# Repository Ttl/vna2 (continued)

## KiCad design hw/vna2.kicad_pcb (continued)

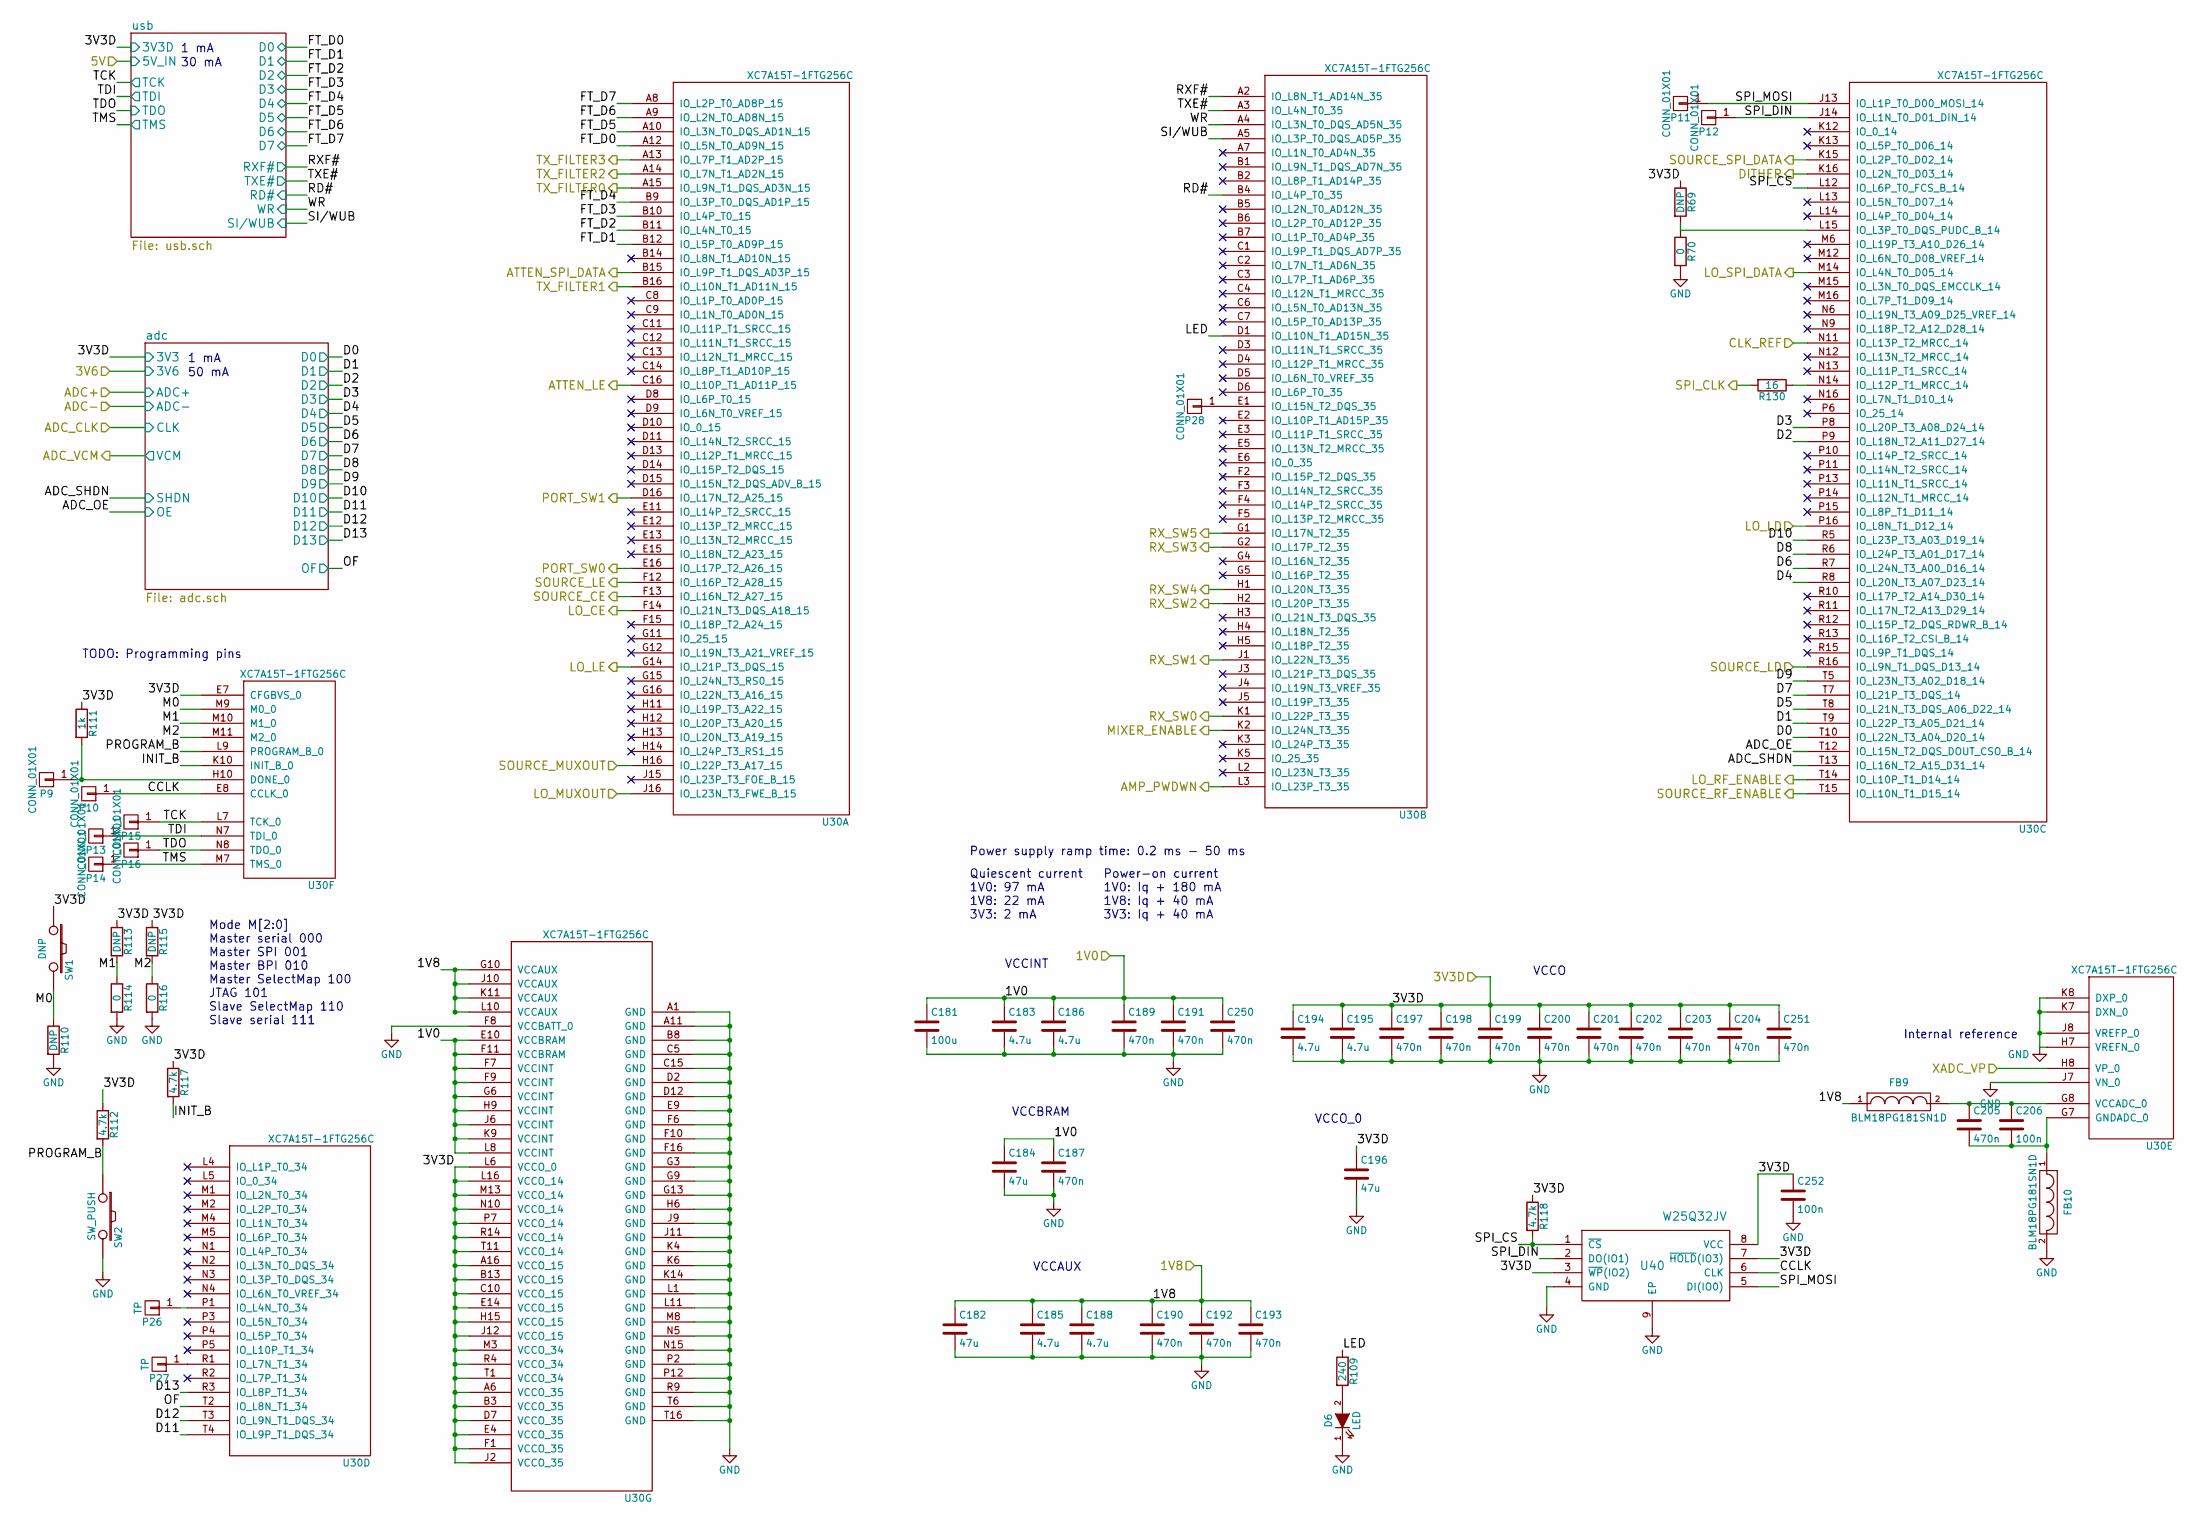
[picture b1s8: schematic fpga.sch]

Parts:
C181: 100u; C_1210
C182, C184, C196: 47u; C_1206
C183, C185, C186, C188, C194, C195: 4.7u; C_0805b
C187, C189, C190, C191, C192, C193, C197, C198, C199, C200, C201, C202, C203, C204, C205, C250, C251: 470n; C_0402b
C206, C252: 100n; C_0402b
D6: LED; LED_0603
FB9, FB10: BLM18PG181SN1D; C_0603b
P9, P10, P11, P12, P13, P14, P15, P16, P28: CONN_01X01; TP_1.00
P26, P27: TP; TP_1.00
R69, R110, R113, R115: DNP; R_0402b
R70, R114, R116: 0; R_0402b
R109: 240; R_0402b
R111: 1k; R_0402b
R112, R117, R118: 4.7k; R_0402b
R130: 16; R_0402b
SW1: DNP; EVP-AWBA2A
SW2: SW_PUSH; EVP-AWBA2A
U30: XC7A15T-1FTG256C; FTG256
U40: W25Q32JV; DFN-S-8-1EP_6x5mm_Pitch1.27mm

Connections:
/1V0: C181.1, C183.1, C184.1, C186.1, C187.1, C189.1, C191.1, C250.1, U30.E10 (VCCBRAM), U30.F7 (VCCINT), U30.F9 (VCCINT), U30.F11 (VCCBRAM), U30.G6 (VCCINT), U30.H9 (VCCINT), U30.J6 (VCCINT), U30.K9 (VCCINT), U30.L8 (VCCINT); also elsewhere on the board
/1V8: C182.1, C185.1, C188.1, C190.1, C192.1, C193.1, FB9.1, U30.G10 (VCCAUX), U30.J10 (VCCAUX), U30.K11 (VCCAUX), U30.L10 (VCCAUX); also elsewhere on the board
/3V3D: C194.1, C195.1, C196.1, C197.1, C198.1, C199.1, C200.1, C201.1, C202.1, C203.1, C204.1, C251.1, C252.1, R69.1, R111.1, R112.1, R113.1, R115.1, R117.1, R118.1, SW1.1, U30.A6 (VCCO_35), U30.A16 (VCCO_15), U30.B3 (VCCO_35), U30.B13 (VCCO_15), U30.C10 (VCCO_15), U30.D7 (VCCO_35), U30.E4 (VCCO_35), U30.E7 (CFGBVS_0), U30.E14 (VCCO_15), U30.F1 (VCCO_35), U30.H15 (VCCO_15), U30.J2 (VCCO_35), U30.J12 (VCCO_15), U30.L6 (VCCO_0), U30.L16 (VCCO_14), U30.M3 (VCCO_34), U30.M13 (VCCO_14), U30.N10 (VCCO_14), U30.P7 (VCCO_14), U30.R4 (VCCO_34), U30.R14 (VCCO_14), U30.T1 (VCCO_34), U30.T11 (VCCO_14), U40.3 (~WP~(IO2)), U40.7 (~HOLD~(IO3)), U40.8 (VCC); also elsewhere on the board
/ATTEN_LE: U30.C16 (IO_L10P_T1_AD11P_15); also elsewhere on the board
/ATTEN_SPI_DATA: U30.B15 (IO_L9P_T1_DQS_AD3P_15); also elsewhere on the board
/CLK_FPGA: U30.N11 (IO_L13P_T2_MRCC_14); also elsewhere on the board
/DITHER: U30.K16 (IO_L2N_T0_D03_14); also elsewhere on the board
/FILTER_V1: U30.A15 (IO_L9N_T1_DQS_AD3N_15); also elsewhere on the board
/FILTER_V2: U30.B16 (IO_L10N_T1_AD11N_15); also elsewhere on the board
/FILTER_V3: U30.A14 (IO_L7N_T1_AD2N_15); also elsewhere on the board
/FILTER_V4: U30.A13 (IO_L7P_T1_AD2P_15); also elsewhere on the board
/LO_CE: U30.F14 (IO_L21N_T3_DQS_A18_15); also elsewhere on the board
/LO_LD: U30.P16 (IO_L8N_T1_D12_14); also elsewhere on the board
/LO_LE: U30.G14 (IO_L21P_T3_DQS_15); also elsewhere on the board
/LO_MUXOUT: U30.J16 (IO_L23N_T3_FWE_B_15); also elsewhere on the board
/LO_RF_ENABLE: U30.T14 (IO_L10P_T1_D14_14); also elsewhere on the board
/LO_SPI_DATA: U30.M14 (IO_L4N_T0_D05_14); also elsewhere on the board
/MIXER_ENABLE: U30.K2 (IO_L24N_T3_35); also elsewhere on the board
/PDET: U30.H8 (VP_0); also elsewhere on the board
/PORT_SW0: U30.E16 (IO_L17P_T2_A26_15); also elsewhere on the board
/PORT_SW1: U30.D16 (IO_L17N_T2_A25_15); also elsewhere on the board
/PWDN: U30.L3 (IO_L23P_T3_35); also elsewhere on the board
/RX_SW0: U30.K1 (IO_L22P_T3_35); also elsewhere on the board
/RX_SW1: U30.J1 (IO_L22N_T3_35); also elsewhere on the board
/RX_SW2: U30.H2 (IO_L20P_T3_35); also elsewhere on the board
/RX_SW3: U30.G2 (IO_L17P_T2_35); also elsewhere on the board
/RX_SW4: U30.H1 (IO_L20N_T3_35); also elsewhere on the board
/RX_SW5: U30.G1 (IO_L17N_T2_35); also elsewhere on the board
/SOURCE_CE: U30.F13 (IO_L16N_T2_A27_15); also elsewhere on the board
/SOURCE_LD: U30.R16 (IO_L9N_T1_DQS_D13_14); also elsewhere on the board
/SOURCE_LE: U30.F12 (IO_L16P_T2_A28_15); also elsewhere on the board
/SOURCE_MUXOUT: U30.H16 (IO_L22P_T3_A17_15); also elsewhere on the board
/SOURCE_RF_ENABLE: U30.T15 (IO_L10N_T1_D15_14); also elsewhere on the board
/SOURCE_SPI_DATA: U30.K15 (IO_L2P_T0_D02_14); also elsewhere on the board
/SPI_CLK: R130.2; also elsewhere on the board
/fpga/ADC_OE: U30.T12 (IO_L15N_T2_DQS_DOUT_CSO_B_14); also elsewhere on the board
/fpga/ADC_SHDN: U30.T13 (IO_L16N_T2_A15_D31_14); also elsewhere on the board
/fpga/CCLK: P10.1, U30.E8 (CCLK_0), U40.6 (CLK)
/fpga/D0: U30.T10 (IO_L22N_T3_A04_D20_14); also elsewhere on the board
/fpga/D1: U30.T9 (IO_L22P_T3_A05_D21_14); also elsewhere on the board
/fpga/D2: U30.P9 (IO_L18N_T2_A11_D27_14); also elsewhere on the board
/fpga/D3: U30.P8 (IO_L20P_T3_A08_D24_14); also elsewhere on the board
/fpga/D4: U30.R8 (IO_L20N_T3_A07_D23_14); also elsewhere on the board
/fpga/D5: U30.T8 (IO_L21N_T3_DQS_A06_D22_14); also elsewhere on the board
/fpga/D6: U30.R7 (IO_L24N_T3_A00_D16_14); also elsewhere on the board
/fpga/D7: U30.T7 (IO_L21P_T3_DQS_14); also elsewhere on the board
/fpga/D8: U30.R6 (IO_L24P_T3_A01_D17_14); also elsewhere on the board
/fpga/D9: U30.T5 (IO_L23N_T3_A02_D18_14); also elsewhere on the board
/fpga/D10: U30.R5 (IO_L23P_T3_A03_D19_14); also elsewhere on the board
/fpga/D11: U30.T4 (IO_L9P_T1_DQS_34); also elsewhere on the board
/fpga/D12: U30.T3 (IO_L9N_T1_DQS_34); also elsewhere on the board
/fpga/D13: U30.R3 (IO_L8P_T1_34); also elsewhere on the board
/fpga/FT_D0: U30.A12 (IO_L5N_T0_AD9N_15); also elsewhere on the board
/fpga/FT_D1: U30.B12 (IO_L5P_T0_AD9P_15); also elsewhere on the board
/fpga/FT_D2: U30.B11 (IO_L4N_T0_15); also elsewhere on the board
/fpga/FT_D3: U30.B10 (IO_L4P_T0_15); also elsewhere on the board
/fpga/FT_D4: U30.B9 (IO_L3P_T0_DQS_AD1P_15); also elsewhere on the board
/fpga/FT_D5: U30.A10 (IO_L3N_T0_DQS_AD1N_15); also elsewhere on the board
/fpga/FT_D6: U30.A9 (IO_L2N_T0_AD8N_15); also elsewhere on the board
/fpga/FT_D7: U30.A8 (IO_L2P_T0_AD8P_15); also elsewhere on the board
/fpga/INIT_B: R117.2, U30.K10 (INIT_B_0)
/fpga/LED: R109.1, U30.D1 (IO_L10N_T1_AD15N_35)
/fpga/M0: R110.1, SW1.2, U30.M9 (M0_0)
/fpga/M1: R113.2, R114.1, U30.M10 (M1_0)
/fpga/M2: R115.2, R116.1, U30.M11 (M2_0)
/fpga/OF: U30.T2 (IO_L8N_T1_34); also elsewhere on the board
/fpga/PROGRAM_B: R112.2, SW2.1, U30.L9 (PROGRAM_B_0)
/fpga/RD#: U30.B4 (IO_L4P_T0_35); also elsewhere on the board
/fpga/RXF#: U30.A2 (IO_L8N_T1_AD14N_35); also elsewhere on the board
/fpga/SI/WUB: U30.A5 (IO_L3P_T0_DQS_AD5P_35); also elsewhere on the board
/fpga/SPI_CS: R118.2, U30.L12 (IO_L6P_T0_FCS_B_14), U40.1 (~CS)
/fpga/SPI_DIN: P12.1, U30.J14 (IO_L1N_T0_D01_DIN_14), U40.2 (DO(IO1))
/fpga/SPI_MOSI: P11.1, U30.J13 (IO_L1P_T0_D00_MOSI_14), U40.5 (DI(IO0))
/fpga/TCK: P15.1, U30.L7 (TCK_0); also elsewhere on the board
/fpga/TDI: P13.1, U30.N7 (TDI_0); also elsewhere on the board
/fpga/TDO: P16.1, U30.N8 (TDO_0); also elsewhere on the board
/fpga/TMS: P14.1, U30.M7 (TMS_0); also elsewhere on the board
/fpga/TXE#: U30.A3 (IO_L4N_T0_35); also elsewhere on the board
/fpga/WR: U30.A4 (IO_L3N_T0_DQS_AD5N_35); also elsewhere on the board
GND: C181.2, C182.2, C183.2, C184.2, C185.2, C186.2, C187.2, C188.2, C189.2, C190.2, C191.2, C192.2, C193.2, C194.2, C195.2, C196.2, C197.2, C198.2, C199.2, C200.2, C201.2, C202.2, C203.2, C204.2, C250.2, C251.2, C252.2, D6.1 (K), FB10.2, R70.2, R110.2, R114.2, R116.2, SW2.2, U30.A1 (GND), U30.A11 (GND), U30.B8 (GND), U30.C5 (GND), U30.C15 (GND), U30.D2 (GND), U30.D12 (GND), U30.E9 (GND), U30.F6 (GND), U30.F8 (VCCBATT_0), U30.F10 (GND), U30.F16 (GND), U30.G3 (GND), U30.G9 (GND), U30.G13 (GND), U30.H6 (GND), U30.H7 (VREFN_0), U30.J7 (VN_0), U30.J8 (VREFP_0), U30.J9 (GND), U30.J11 (GND), U30.K4 (GND), U30.K6 (GND), U30.K7 (DXN_0), U30.K8 (DXP_0), U30.K14 (GND), U30.L1 (GND), U30.L11 (GND), U30.M8 (GND), U30.N5 (GND), U30.N15 (GND), U30.P2 (GND), U30.P12 (GND), U30.R9 (GND), U30.T6 (GND), U30.T16 (GND), U40.4 (GND), U40.9 (EP); also elsewhere on the board
unnamed: C205.1, C206.1, FB9.2, U30.G8 (VCCADC_0)
unnamed: C205.2, C206.2, FB10.1, U30.G7 (GNDADC_0)
unnamed: D6.2 (A), R109.2
unnamed: P9.1, R111.2, U30.H10 (DONE_0)
unnamed: P26.1, U30.P1 (IO_L4N_T0_34)
unnamed: P27.1, U30.R1 (IO_L7N_T1_34)
unnamed: P28.1, U30.E1 (IO_L15N_T2_DQS_35)
unnamed: R69.2, R70.1, U30.L15 (IO_L3P_T0_DQS_PUDC_B_14)
unnamed: R130.1, U30.N14 (IO_L12P_T1_MRCC_14)

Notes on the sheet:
VCCINT
VCCBRAM
VCCAUX
VCCO_0
VCCO
Internal reference
Quiescent current 1V0: 97 mA 1V8: 22 mA 3V3: 2 mA
Power-on current 1V0: Iq + 180 mA 1V8: Iq + 40 mA 3V3: Iq + 40 mA
Power supply ramp time: 0.2 ms - 50 ms
50 mA
TODO: Programming pins
Mode M[2:0] Master serial 000 Master SPI 001 Master BPI 010 Master SelectMap 100 JTAG 101 Slave SelectMap 110 Slave serial 111
30 mA
1 mA

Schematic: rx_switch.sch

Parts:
C8, C9, C12, C28: 1n; C_0402b
C35, C36, C54, C77, C81, C82, C83, C84, C85: 18p; C_0402b
C78, C80, C87, C253, C254: 100n; C_0402b
C271, C272: DNP; C_0805b
F7, F8, F9, F10, F11, F12, F13, F14, F15, F16, F17, F18: Via; RF_via
FB11: BLM18PG181SN1D; C_0603b
R1, R2, R3, R4, R8, R9: 10; R_0402b
R5, R7, R10: 100; R_0402b
U6, U10, U11: PE42420; TFLGA-20

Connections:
3V3A_RX: C253.1, FB11.1; also elsewhere on the board
/A: C9.1, F10.1, F14.1; also elsewhere on the board
/B: C28.1, F8.1, F12.1; also elsewhere on the board
/RX1: C8.1, F9.1, F13.1; also elsewhere on the board
/RX2: C12.1, F7.1, F11.1; also elsewhere on the board
/RX_SW0: C36.2, R1.1; also elsewhere on the board
/RX_SW1: C35.2, R3.1; also elsewhere on the board
/RX_SW2: C77.2, R2.1; also elsewhere on the board
/RX_SW3: C54.2, R4.1; also elsewhere on the board
/RX_SW4: C84.2, R8.1; also elsewhere on the board
/RX_SW5: C83.2, R9.1; also elsewhere on the board
/receiver/RF_IN: U11.8 (RFC); also elsewhere on the board
/receiver/RX switch/3V3: C78.1, C80.1, C87.1, C254.1, C271.1, C272.1, FB11.2, R5.1, R7.1, R10.1
GND: C35.1, C36.1, C54.1, C77.1, C78.2, C80.2, C81.2, C82.2, C83.1, C84.1, C85.2, C87.2, C253.2, C254.2, C271.2, C272.2, F7.2, F8.2, F9.2, F10.2, F11.2, F12.2, F13.2, F14.2, F15.2, F16.2, F17.2, F18.2, U6.1 (GND), U6.2 (GND), U6.4 (GND), U6.5 (GND), U6.6 (GND), U6.7 (GND), U6.9 (GND), U6.10 (GND), U6.11 (GND), U6.12 (GND), U6.14 (GND), U6.15 (GND), U6.18 (GND), U6.19 (GND), U6.EP, U10.1 (GND), U10.2 (GND), U10.4 (GND), U10.5 (GND), U10.6 (GND), U10.7 (GND), U10.9 (GND), U10.10 (GND), U10.11 (GND), U10.12 (GND), U10.14 (GND), U10.15 (GND), U10.18 (GND), U10.19 (GND), U10.EP, U11.1 (GND), U11.2 (GND), U11.4 (GND), U11.5 (GND), U11.6 (GND), U11.7 (GND), U11.9 (GND), U11.10 (GND), U11.11 (GND), U11.12 (GND), U11.14 (GND), U11.15 (GND), U11.18 (GND), U11.19 (GND), U11.EP; also elsewhere on the board
unnamed: C8.2, U6.3 (RF1)
unnamed: C9.2, U6.13 (RF2)
unnamed: C12.2, U10.3 (RF1)
unnamed: C28.2, U10.13 (RF2)
unnamed: C81.1, R5.2, U6.20 (VDD)
unnamed: C82.1, R7.2, U10.20 (VDD)
unnamed: C85.1, R10.2, U11.20 (VDD)
unnamed: F15.1, F17.1, U6.8 (RFC), U11.3 (RF1)
unnamed: F16.1, F18.1, U10.8 (RFC), U11.13 (RF2)
unnamed: R1.2, U6.16 (CTRL2)
unnamed: R2.2, U10.16 (CTRL2)
unnamed: R3.2, U6.17 (CTRL1)
unnamed: R4.2, U10.17 (CTRL1)
unnamed: R8.2, U11.16 (CTRL2)
unnamed: R9.2, U11.17 (CTRL1)

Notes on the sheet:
PE4240 switch control truth table: CTRL1 CTRL2 RFC-RF1 RFC-RF2 Low Low Off Off Low High Off On High Low On Off High High N/A N/A
Port A1 A2 B1 B2 C1 C2 RF1 1 0 0 0 1 0 RF2 0 1 0 0 1 0 RF3 0 0 1 0 0 1 RF4 0 0 0 1 0 1

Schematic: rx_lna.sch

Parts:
C88: DNP; C_0805b
C89, C91: 100n; C_0402b
C90, C121: 1n; C_0402b
C113: 10u; C_0805b
C115: 10p; C_0402b
C120: 10n; C_0402b
C259: DNP; C_0402b
F5, F6: Via; RF_via
FB8: BLM18PG181SN1D; C_0603b
L1: AISC-0603HP-R10J; C_0603b
R14: 0; R_0402b
R21: 1.8; R_0603b
U12: TRF37A75; DFN-8-1EP_2x2mm_Pitch0.5mm

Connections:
/5V: C88.1, C89.1, FB8.1; also elsewhere on the board
/receiver/RF_BALUN: C121.1; also elsewhere on the board
/receiver/RF_IN: C90.2, F5.1, F6.1; also elsewhere on the board
GND: C88.2, C89.2, C91.2, C113.2, C115.2, C120.2, C259.1, F5.2, F6.2, R14.2, U12.3 (NC), U12.4 (NC), U12.6 (NC), U12.8 (NC), U12.9 (GND); also elsewhere on the board
unnamed: C90.1, U12.2 (RFIN)
unnamed: C91.1, C113.1, FB8.2, R21.1, U12.1 (VCC)
unnamed: C115.1, C120.1, L1.1, R21.2
unnamed: C121.2, C259.2, L1.2, U12.7 (RFOUT)
unnamed: R14.1, U12.5 (PWDN)

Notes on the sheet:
Gain: 11 - 13 dB
95 mA

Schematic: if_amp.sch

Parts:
C122, C123, C124, C125, C126, C127, C138: DNP; C_0402b
C128, C144, C146: 18p; C_0402b
C135, C154, C156: 100p; C_0402b
C139, C148, C149: 100n; C_0402b
C140: 36p; C_0402b
C155: 220p; C_0402b
C262: DNP; C_0805b
L3, L8: 1u; C_0603b
R22, R23, R24, R28: 0; R_0402b
R39: DNP; R_0402b
R40, R41, R42: 1k; R_0402b
R43, R44: 3.3k; R_0402b
R45, R46: 50; R_0402b
U21: ADA4940-1; VFQFN-16

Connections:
3V3A_RX: C148.1, C262.1, U21.5 (+VS), U21.6 (+VS), U21.7 (+VS), U21.8 (+VS), U21.12 (~DISABLE); also elsewhere on the board
/ADC+: C155.2, C156.1, R46.1; also elsewhere on the board
/ADC-: C154.2, C155.1, R45.1; also elsewhere on the board
/ADC_VCM: C149.1, U21.9 (VOCM); also elsewhere on the board
/receiver/DITHER: C139.2; also elsewhere on the board
/receiver/IF+: R23.2; also elsewhere on the board
/receiver/IF-: R22.2; also elsewhere on the board
GND: C122.1, C124.2, C125.1, C127.2, C138.2, C148.2, C149.2, C154.1, C156.2, C262.2, U21.13 (-VS), U21.14 (-VS), U21.15 (-VS), U21.16 (-VS), U21.EP; also elsewhere on the board
unnamed: C122.2, C123.1, R22.1, R24.2
unnamed: C123.2, C124.1, R23.1, R28.2
unnamed: C125.2, C126.1, C128.1, L3.1, R24.1
unnamed: C126.2, C127.1, C128.2, L8.1, R28.1
unnamed: C135.1, C140.2, L3.2, R41.2
unnamed: C135.2, C140.1, L8.2, R40.2
unnamed: C138.1, R39.2
unnamed: C139.1, R42.2
unnamed: C144.1, R43.1, U21.1 (-FB)
unnamed: C144.2, R39.1, R40.1, R43.2, U21.2 (+IN)
unnamed: C146.1, R44.1, U21.4 (+FB)
unnamed: C146.2, R41.1, R42.1, R44.2, U21.3 (-IN)
unnamed: R45.2, U21.10 (+OUT)
unnamed: R46.2, U21.11 (-OUT)

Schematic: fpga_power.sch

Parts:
C230, C231, C232, C233, C240, C241, C242, C243, C244, C245, C246, C247: 10u; C_0805b
C234, C235: 10n; C_0402b
C236: 36p; C_0402b
C237: 33p; C_0402b
C238: 16n; C_0402b
C239: 18n; C_0402b
D1, D4: SS13FL; SOD-123F
L9, L10: 33u (SRR6040A-330M); SRR6040A
R86: DNP; R_0402b
R87: 0; R_0402b
R96, R98: 68k; R_0402b
R99: 15k; R_0402b
R100: 16k; R_0402b
R101, R103: 4.99k; R_0402b
R102: 7.5k; R_0402b
R104: 2.5k; R_0402b
R105, R106: 33; R_0402b
U37, U38: L7980; DFN-8-1EP_3x3mm_Pitch0.5mm

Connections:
/1V0: C240.1, C243.1, C244.1, C246.1, L9.2, R101.1, R105.1; also elsewhere on the board
/1V8: C241.1, C242.1, C245.1, C247.1, L10.2, R103.1, R106.1; also elsewhere on the board
/5V: U37.3 (EN), U38.3 (EN); also elsewhere on the board
/power/12V: C230.1, C231.1, C232.1, C233.1, U37.8 (VCC), U38.8 (VCC); also elsewhere on the board
/power/SYNC_3V3: R86.2; also elsewhere on the board
/power/fpga_power/SYNC_1V0: R86.1, R87.2, U37.2 (SYNCH)
/power/fpga_power/SYNC_1V8: R87.1, U38.2 (SYNCH)
GND: C230.2, C231.2, C232.2, C233.2, C240.2, C241.2, C242.2, C243.2, C244.2, C245.2, C246.2, C247.2, D1.2 (A), D4.2 (A), R96.2, R98.2, R102.2, R104.2, U37.7 (GND), U37.9 (EP), U38.7 (GND), U38.9 (EP); also elsewhere on the board
unnamed: C234.1, R99.2
unnamed: C234.2, C236.2, C238.2, R101.2, R102.1, U37.5 (FB)
unnamed: C235.1, R100.2
unnamed: C235.2, C237.2, C239.2, R103.2, R104.1, U38.5 (FB)
unnamed: C236.1, R99.1, U37.4 (COMP)
unnamed: C237.1, R100.1, U38.4 (COMP)
unnamed: C238.1, R105.2
unnamed: C239.1, R106.2
unnamed: D1.1 (K), L9.1, U37.1 (OUT)
unnamed: D4.1 (K), L10.1, U38.1 (OUT)
unnamed: R96.1, U37.6 (FSW)
unnamed: R98.1, U38.6 (FSW)

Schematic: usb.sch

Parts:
C207, C210, C211, C212, C213, C214, C215: 100n; C_0402b
C208, C209: 33p; C_0402b
C263: DNP; C_0805b
FB12: BLM18PG181SN1D; C_0603b
R71: 4.7k; R_0402b
R72, R73: 10k; R_0402b
R79: 2k2; R_0402b
R80, R81: 27; R_0402b
R82: 1k5; R_0402b
R83: 470; R_0402b
R84, R85, R88: 33; R_0402b
U31: USB-MICRO; USB_MICRO
U32: 93LC46B; SOT-23-6
U33: FT2232D; LQFP-48_7x7mm_Pitch0.5mm
Y1: ABMM-6.000MHZ; ABMM

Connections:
/3V3D: C211.1, C212.1, U33.10 (SI/WUA), U33.14 (VCCIOA), U33.31 (VCCIOB); also elsewhere on the board
/5V: FB12.1; also elsewhere on the board
/fpga/FT_D0: U33.40 (BDBUS0); also elsewhere on the board
/fpga/FT_D1: U33.39 (BDBUS1); also elsewhere on the board
/fpga/FT_D2: U33.38 (BDBUS2); also elsewhere on the board
/fpga/FT_D3: U33.37 (BDBUS3); also elsewhere on the board
/fpga/FT_D4: U33.36 (BDBUS4); also elsewhere on the board
/fpga/FT_D5: U33.35 (BDBUS5); also elsewhere on the board
/fpga/FT_D6: U33.33 (BDBUS6); also elsewhere on the board
/fpga/FT_D7: U33.32 (BDBUS7); also elsewhere on the board
/fpga/RD#: U33.28 (BCBUS2/RD#); also elsewhere on the board
/fpga/RXF#: U33.30 (BCBUS0/RXF#); also elsewhere on the board
/fpga/SI/WUB: U33.26 (SI/WUB); also elsewhere on the board
/fpga/TCK: R84.1; also elsewhere on the board
/fpga/TDI: R88.1; also elsewhere on the board
/fpga/TDO: U33.22 (ADBUS2/TDO); also elsewhere on the board
/fpga/TMS: R85.1; also elsewhere on the board
/fpga/TXE#: U33.29 (BCBUS1/TXE#); also elsewhere on the board
/fpga/WR: U33.27 (BCBUS3/WR); also elsewhere on the board
/fpga/usb/5V: C207.1, C214.1, C215.1, C263.1, FB12.2, R73.1, R83.1, U32.6 (VCC), U33.3 (VCC), U33.42 (VCC)
/fpga/usb/DO: R73.2, R79.1, U32.1 (DO)
/fpga/usb/EECS: U32.5 (CS), U33.48 (EECS)
/fpga/usb/EEDATA: R79.2, U32.3 (DI), U33.2 (EEDATA)
/fpga/usb/EESK: U32.4 (CLK), U33.1 (EESK)
/fpga/usb/USBDM: R80.2, U31.2 (D-)
/fpga/usb/USBDP: R81.2, U31.3 (D+)
/fpga/usb/USB_5V: R71.1, U31.1 (VCC)
GND: C207.2, C208.2, C209.2, C210.2, C211.2, C212.2, C213.2, C214.2, C215.2, C263.2, R72.2, U31.5 (GND), U32.2 (VSS), U33.9 (GND), U33.18 (GND), U33.25 (GND), U33.34 (GND), U33.45 (AGND), U33.47 (TEST), Y1.2, Y1.4; also elsewhere on the board
unnamed: C208.1, U33.43 (XTIN), Y1.1
unnamed: C209.1, U33.44 (XTOUT), Y1.3
unnamed: C210.1, U33.6 (3V3OUT)
unnamed: C213.1, R83.2, U33.46 (AVCC)
unnamed: R71.2, R72.1, U33.4 (RESET#)
unnamed: R80.1, U33.8 (USBDM)
unnamed: R81.1, R82.1, U33.7 (USBDP)
unnamed: R82.2, U33.5 (RSTOUT#)
unnamed: R84.2, U33.24 (ADBUS0/TCK)
unnamed: R85.2, U33.21 (ADBUS3/TMS)
unnamed: R88.2, U33.23 (ADBUS1/TDI)

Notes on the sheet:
30 mA

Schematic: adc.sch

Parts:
C216, C220: 2.2u; C_0603b
C217, C218, C222, C249: 1u; C_0603b
C219, C221, C223, C224, C225: 100n; C_0402b
C248: 10u; C_0805b
R91, R93: 0; R_0402b
R92: DNP; R_0402b
U34: LTC2247; QFN-32-1EP_5x5mm_Pitch0.5mm
U39: LP5907-3V0; SOT-23-5

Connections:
/3V3D: C225.1, U34.21 (OVDD); also elsewhere on the board
/3V6: C248.1, U39.1 (IN), U39.3 (EN); also elsewhere on the board
/ADC+: U34.1 (AIN+); also elsewhere on the board
/ADC-: U34.2 (AIN-); also elsewhere on the board
/ADC_VCM: C216.1, C219.1, U34.31 (VCM); also elsewhere on the board
/CLK_ADC: U34.9 (CLK); also elsewhere on the board
/fpga/ADC_OE: U34.11 (~OE); also elsewhere on the board
/fpga/ADC_SHDN: U34.10 (SHDN); also elsewhere on the board
/fpga/D0: U34.12 (D0); also elsewhere on the board
/fpga/D1: U34.13 (D1); also elsewhere on the board
/fpga/D2: U34.14 (D2); also elsewhere on the board
/fpga/D3: U34.15 (D3); also elsewhere on the board
/fpga/D4: U34.16 (D4); also elsewhere on the board
/fpga/D5: U34.17 (D5); also elsewhere on the board
/fpga/D6: U34.18 (D6); also elsewhere on the board
/fpga/D7: U34.19 (D7); also elsewhere on the board
/fpga/D8: U34.22 (D8); also elsewhere on the board
/fpga/D9: U34.23 (D9); also elsewhere on the board
/fpga/D10: U34.24 (D10); also elsewhere on the board
/fpga/D11: U34.25 (D11); also elsewhere on the board
/fpga/D12: U34.26 (D12); also elsewhere on the board
/fpga/D13: U34.27 (D13); also elsewhere on the board
/fpga/OF: U34.28 (OF); also elsewhere on the board
/fpga/adc/3V0: C222.1, C223.1, C224.1, C249.1, R91.1, R93.2, U34.7 (VDD), U34.32 (VDD), U39.5 (OUT)
/fpga/adc/REFH: C217.1, C220.1, C221.1, U34.3 (REFH), U34.4 (REFH)
/fpga/adc/REFL: C218.1, C220.2, C221.2, U34.5 (REFL), U34.6 (REFL)
GND: C216.2, C217.2, C218.2, C219.2, C222.2, C223.2, C224.2, C225.2, C248.2, C249.2, R92.2, U34.8 (GND), U34.20 (OGND), U34.33 (GND), U39.2 (GND); also elsewhere on the board
unnamed: R91.2, R92.1, U34.29 (MODE)
unnamed: R93.1, U34.30 (SENSE)

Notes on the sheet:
50 mA

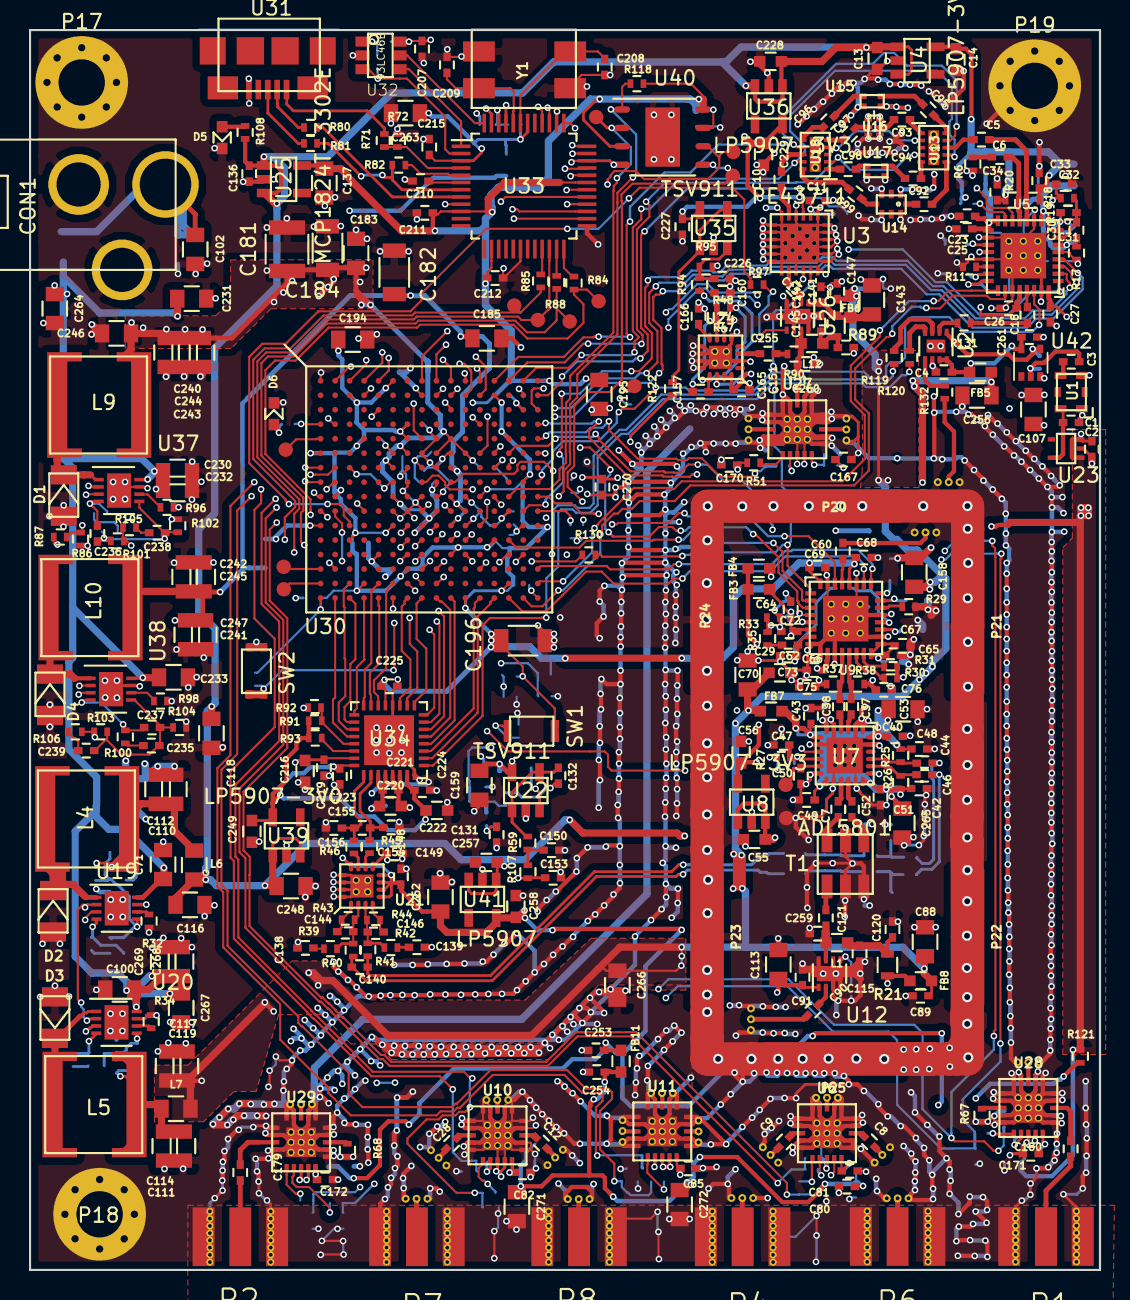
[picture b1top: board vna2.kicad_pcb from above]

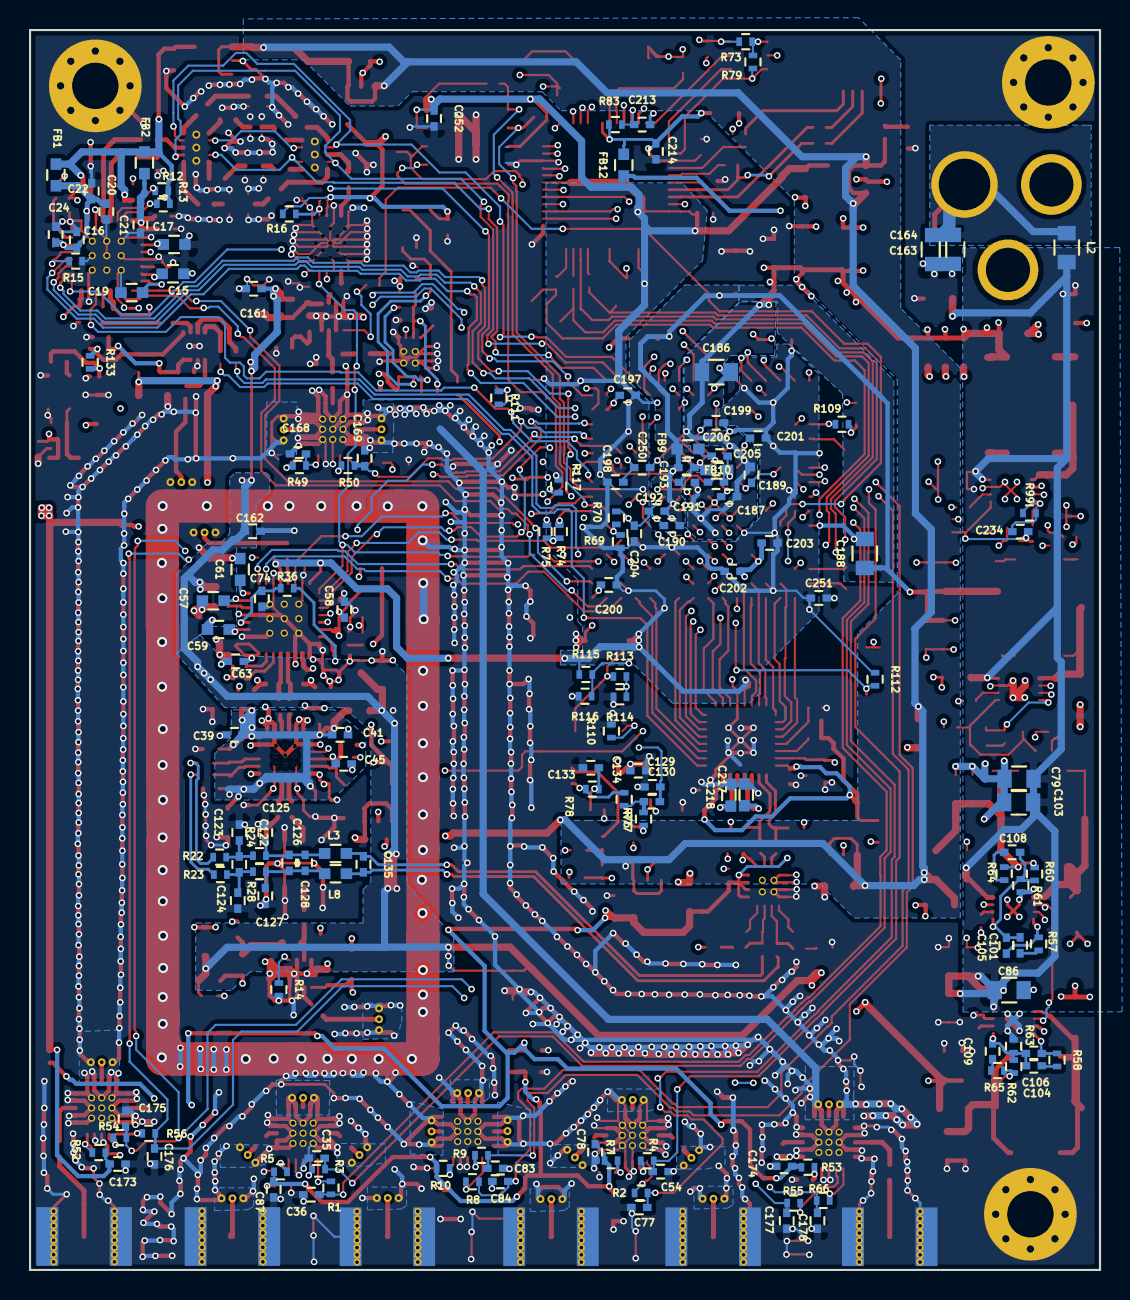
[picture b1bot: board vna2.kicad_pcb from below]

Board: 4 copper layers, 73.9 x 85.7 mm, 522 parts (148 on the bottom side), 310 nets.

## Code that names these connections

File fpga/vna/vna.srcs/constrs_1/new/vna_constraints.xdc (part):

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set_property PACKAGE_PIN T3 [get_ports {adc_in[12]}]
set_property PACKAGE_PIN R3 [get_ports {adc_in[13]}]
set_property PACKAGE_PIN T2 [get_ports adc_of]
set_property PACKAGE_PIN T12 [get_ports adc_oe]
set_property PACKAGE_PIN T13 [get_ports adc_shdn]

set_property PACKAGE_PIN A13 [get_ports {tx_filter[3]}]
set_property PACKAGE_PIN A14 [get_ports {tx_filter[2]}]
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set_property PACKAGE_PIN B12 [get_ports {ft2232_data[1]}]
set_property PACKAGE_PIN A12 [get_ports {ft2232_data[0]}]

set_property PACKAGE_PIN A2 [get_ports rxf]
set_property PACKAGE_PIN A3 [get_ports txe]
set_property PACKAGE_PIN A4 [get_ports wr]
set_property PACKAGE_PIN A5 [get_ports si_wu]
set_property PACKAGE_PIN B4 [get_ports rd]

set_property PACKAGE_PIN K16 [get_ports dither]

set_property PACKAGE_PIN K2 [get_ports mixer_enable]
set_property PACKAGE_PIN L3 [get_ports amp_pwdn]

set_property PACKAGE_PIN N14 [get_ports spi_clk]
set_property PACKAGE_PIN M14 [get_ports lo_spi_data]
set_property PACKAGE_PIN K15 [get_ports source_spi_data]
set_property PACKAGE_PIN G14 [get_ports lo_le]
set_property PACKAGE_PIN F14 [get_ports lo_ce]
set_property PACKAGE_PIN F12 [get_ports source_le]
set_property PACKAGE_PIN F13 [get_ports source_ce]
set_property PACKAGE_PIN C16 [get_ports atten_le]
set_property PACKAGE_PIN B15 [get_ports atten_spi_data]
set_property PACKAGE_PIN P16 [get_ports lo_ld]
set_property PACKAGE_PIN R16 [get_ports source_ld]
set_property PACKAGE_PIN H16 [get_ports source_muxout]
set_property PACKAGE_PIN J16 [get_ports lo_muxout]

set_property PACKAGE_PIN T14 [get_ports lo_rf_enable]
set_property PACKAGE_PIN T15 [get_ports source_rf_enable]

set_property PACKAGE_PIN D1 [get_ports led]

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
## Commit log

2017-03-10 Single process FT2232D communication
2017-03-21 Add coupler design files
2017-05-06 Update PC code
    Add switch terms. Tune PLL registers. Don't write unnecessary values.
2017-05-26 Add send immediate pin logic for FT2232D
    When last byte of the IQ packet has been sent to the FT2232D toggle
    SI_WU pin to immediately initiate USB transfer to host.
2017-07-06 Add papilio-loader patch for Artix-7
2017-07-06 Add FPGA bit stream
2017-07-27 Update components values
    Change IF amplifier to ADA4940. Same footprint, no changes in PCB.
    Fix M[0:2] connections.
2017-07-27 Add openocd scripts for programming FPGA and SPI flash
2018-01-28 Fix ferrite bead amounts in coupler BOM
2025-01-23 Update software for modern Python
